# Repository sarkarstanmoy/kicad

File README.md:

# kicad
KiCad for electornics project

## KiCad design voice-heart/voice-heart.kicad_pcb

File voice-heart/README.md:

# Voice-Message Heart

A heart-shaped gift: press the big button in the middle and it plays a recorded voice
message while 10 red LEDs light up around the edge, stay on for about the length of the
message, then slowly fade out. Hold the small **REC** button to record a new message
(up to 10 s). The message stays even with the batteries removed.

| File | What it is |
|---|---|
| `voice-heart.kicad_pro` | KiCad 10 project (open this) |
| `voice-heart.kicad_sch` | Schematic, with supplier and price fields on every part |
| `voice-heart.kicad_pcb` | Heart-shaped 2-layer PCB, 96 x 86 mm, all through-hole |
| `voice-heart.kicad_sym` / `voice-heart.pretty/` | ISD1820 module symbol and footprint (blue 2x6-header board) |
| `voice-heart.kicad_dru` | Lion Circuits manufacturing limits as KiCad DRC rules |
| `docs/voice-heart-schematic.pdf` | Printable schematic |
| `docs/voice-heart-bom.csv` | Parts list |
| `docs/pcb-front.png`, `docs/pcb-back.png` | 3D renders |
| `fab/voice-heart-gerbers.zip` | Upload this to the PCB maker |

## How it works

| Block | Parts | What it does |
|---|---|---|
| Power | 3x AAA box with switch and screw lid (4.5 V) | No coin cells, so nothing small and dangerous to swallow |
| Voice | ISD1820 module (blue board) with its 8 Ω speaker plugged into the module | Records from its onboard mic while REC is held, plays the whole message on a PLAY press |
| Buttons | SW1 12 mm PLAY (front centre), SW2 6 mm REC (left lobe) | Both pull the module's REC/PLAYE pins up to the battery (active HIGH) |
| Glow timer | D11, D12, C1 22 µF, R11 470k, Q1 BC517 | A press charges C1; C1 drains slowly into Q1's base, so Q1 keeps the LEDs on about 10 s, then they fade over about 15 s |
| Heart LEDs | D1–D10 red 5 mm, R1–R10 330 Ω | About 6 mA each, about 60 mA total while glowing |

Want a longer glow? Swap C1 for 47 µF (about twice as long). Shorter? Use 10 µF.

Battery life: about 0 mA when idle (and the box has its own switch), about 80 mA while
playing. Hundreds of plays per set of AAAs.

## Ordering the board (Lion Circuits, cheapest settings)

Upload `fab/voice-heart-gerbers.zip` at [lioncircuits.com/quote](https://www.lioncircuits.com/quote)
and **keep every default**:

| Setting | Value |
|---|---|
| Quantity | 5 (minimum) |
| Board size | 96 x 86 mm (read from the Gerbers) |
| Layers | 2, single PCB, 1 design |
| Material / thickness | FR4-TG135, 1.6 mm |
| Copper / finish | 1 oz, HASL |
| Mask colour | **Green** (any other colour adds ₹500) |
| Service | Standard (5–6 days), DTDC Standard shipping (free) |

Quoted 13 Nov 2026: **₹1,652 + 18% GST = ₹1,949** for 5 boards, delivered.

The design is checked against Lion Circuits' standard limits (`voice-heart.kicad_dru`):
6 mil tracks/spacing, 12 mil via-to-track, 0.35 mm minimum drill, 6 mil annular ring,
6 mil silkscreen. The board uses 0.5 mm tracks, 0.3 mm spacing and 0.45 mm via drills, so
it passes with margin.

## Parts (about ₹250–350 plus the PCB)

See `docs/voice-heart-bom.csv`. Ask for the **blue ISD1820 module with speaker**
(Robu.in: "ISD1820 Recording Module Voice Board With On Board Mic and Loud Speaker"),
a **3x AAA box with switch and screw cover**, a BC517 Darlington transistor, and red
5 mm LEDs. No separate speaker is needed.

## Soldering order

Lowest parts first, so the board sits flat on the bench:

1. R1–R11 (resistors, standing upright). R11 is the 470k; the other ten are 330.
2. D11, D12 (1N4148): the black band goes on the side marked **K**.
3. Q1 (BC517): its flat face matches the silkscreen.
4. C1 (22 µF): the long leg (+) goes in the hole marked **+**.
5. D1–D10 (LEDs): the **long leg goes in the round pad**, the short leg in the square pad.
6. SW2 (REC) and SW1 (PLAY, big button).
7. Back side: solder a **2x6 female header** (or two 1x6 strips cut from a 1x40 strip)
   onto U1's 12 holes. The blue ISD1820 plugs in **component side down**, its header pins
   into this socket, so the module covers the back of the PLAY button. The socket
   height keeps the trimmed legs underneath clear of the module.
8. Speaker: plug its white connector into the module's speaker socket and glue the
   speaker to the back.
9. Battery box: red wire to **+**, black to **−** on the BATTERY pads. Glue the box to
   the back; it also works as a stand. A dab of hot glue over each wire joint stops the
   wires breaking.
10. Trim every leg flush on the back, then cover the back with felt or a 3D-printed
    plate so there are no sharp points.

> **Check before plugging in:** the back of the heart labels the module column
> **VCC, GND, FT, P-L, P-E, REC**, matching the blue ISD1820's own silkscreen. The other
> column ("JUMPERS") is the module's RPL/FT jumper pins and is not connected. **Remove
> any jumper caps** on the module, or it will loop or pass the mic through.

## Recording a message

1. Switch the battery box ON.
2. Hold **REC**, wait half a second, speak clearly about 10–20 cm from the module's mic,
   and let go within 10 seconds. The heart glows while you record.
3. Press the big heart button to hear it back.

Record again any time; the new message replaces the old one.

## Safety (for an 8-year-old)

- AAA box with a **screw-shut lid**: batteries can't fall out.
- No coin cells, no LiPo, nothing gets hot (about 80 mA from 4.5 V).
- Trim the legs and cover the back so there are no sharp points.
- Speaker volume is modest, comfortable at arm's length.

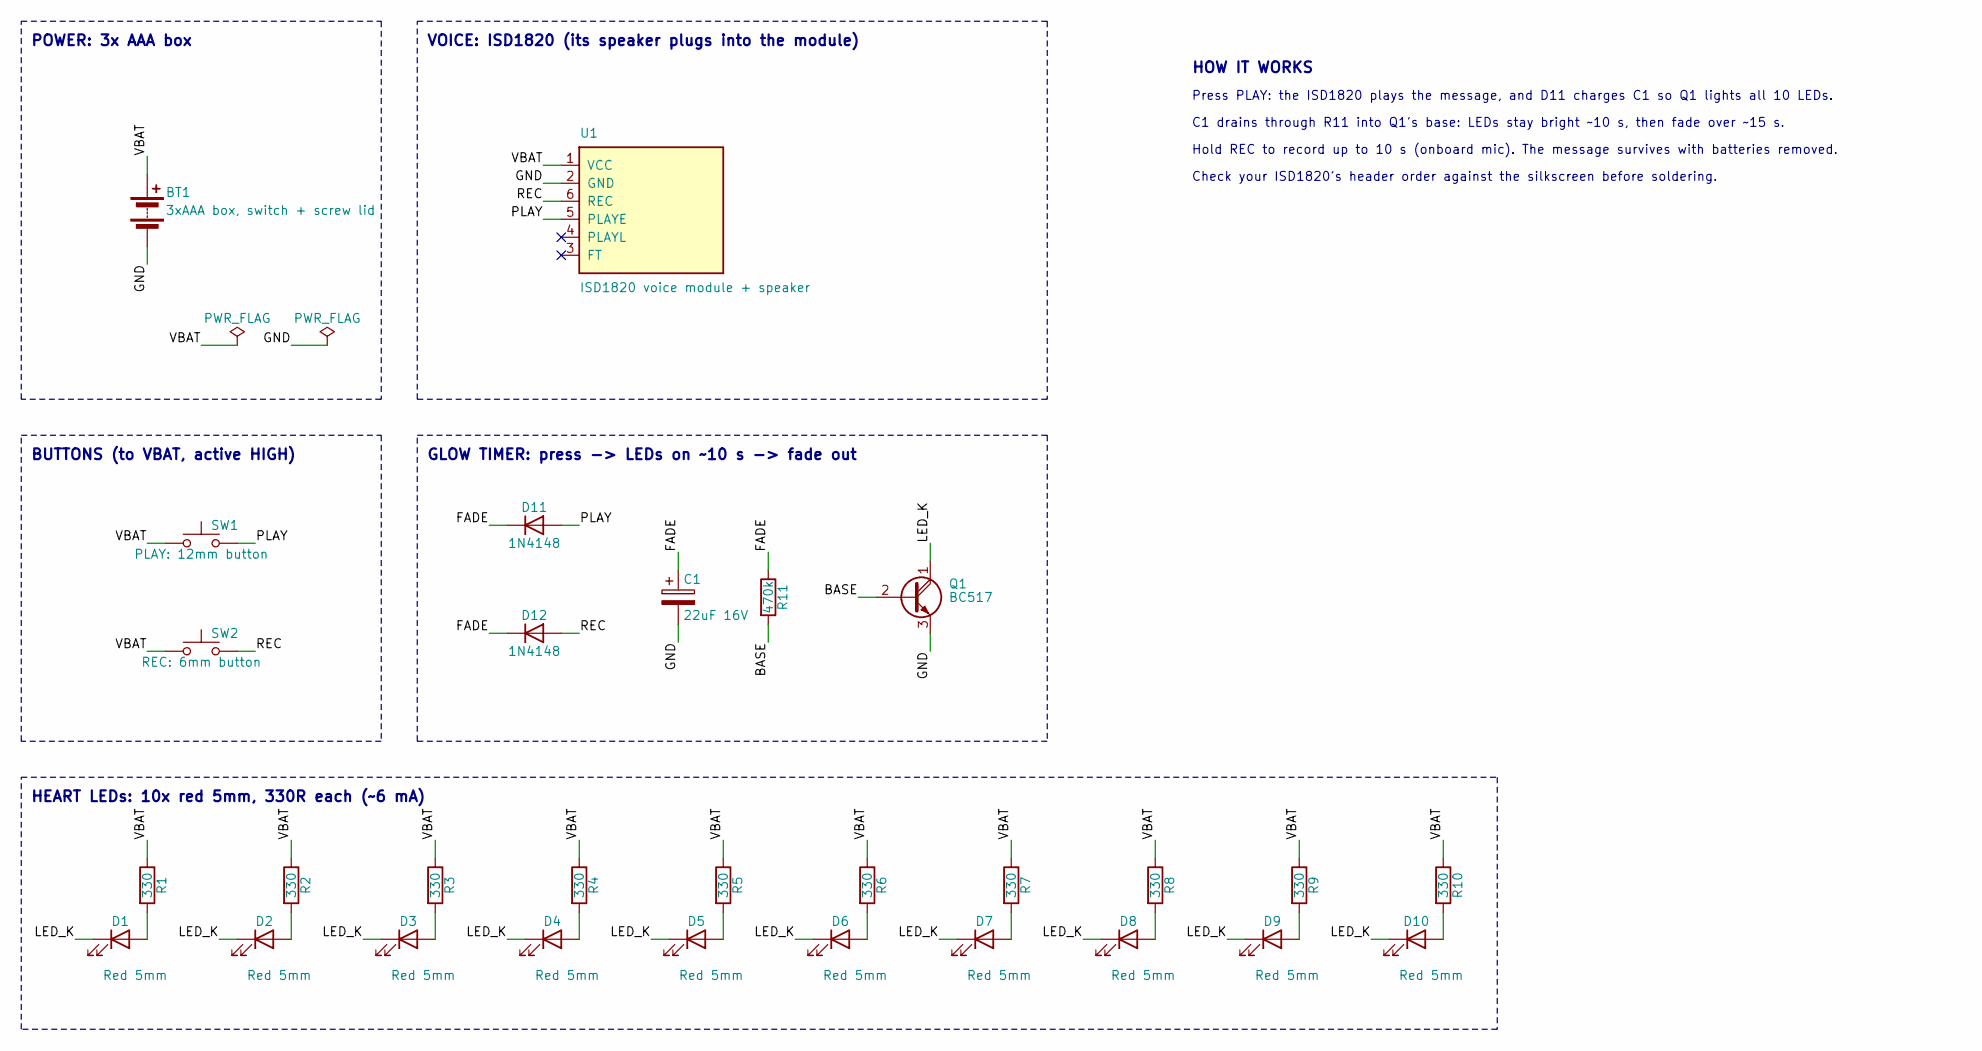
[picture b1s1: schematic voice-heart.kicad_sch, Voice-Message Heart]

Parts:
BT1: 3xAAA box, switch + screw lid; SolderWire-0.25sqmm_1x02_P4.2mm_D0.65mm_OD1.7mm
C1: 22uF 16V; CP_Radial_D5.0mm_P2.00mm
D1, D2, D3, D4, D5, D6, D7, D8, D9, D10: Red 5mm; LED_D5.0mm
D11, D12: 1N4148; D_DO-35_SOD27_P7.62mm_Horizontal
Q1: BC517; TO-92_Inline_Wide
R1, R2, R3, R4, R5, R6, R7, R8, R9, R10: 330; R_Axial_DIN0204_L3.6mm_D1.6mm_P2.54mm_Vertical
R11: 470k; R_Axial_DIN0204_L3.6mm_D1.6mm_P2.54mm_Vertical
SW1: PLAY: 12mm button; SW_PUSH-12mm
SW2: REC: 6mm button; SW_PUSH_6mm
U1: ISD1820 voice module + speaker; ISD1820_Module

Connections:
/BASE: Q1.2 (B), R11.2
/FADE: C1.1, D11.1 (K), D12.1 (K), R11.1
/GND: BT1.2 (-), C1.2, Q1.3 (E), U1.2 (GND)
/LED_K: D1.1 (K), D2.1 (K), D3.1 (K), D4.1 (K), D5.1 (K), D6.1 (K), D7.1 (K), D8.1 (K), D9.1 (K), D10.1 (K), Q1.1 (C)
/PLAY: D11.2 (A), SW1.2, U1.5 (PLAYE)
/REC: D12.2 (A), SW2.2, U1.6 (REC)
/VBAT: BT1.1 (+), R1.1, R2.1, R3.1, R4.1, R5.1, R6.1, R7.1, R8.1, R9.1, R10.1, SW1.1, SW2.1, U1.1 (VCC)
unnamed: D1.2 (A), R1.2
unnamed: D2.2 (A), R2.2
unnamed: D3.2 (A), R3.2
unnamed: D4.2 (A), R4.2
unnamed: D5.2 (A), R5.2
unnamed: D6.2 (A), R6.2
unnamed: D7.2 (A), R7.2
unnamed: D8.2 (A), R8.2
unnamed: D9.2 (A), R9.2
unnamed: D10.2 (A), R10.2

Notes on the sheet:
POWER: 3x AAA box
VOICE: ISD1820 (its speaker plugs into the module)
BUTTONS (to VBAT, active HIGH)
GLOW TIMER: press -> LEDs on ~10 s -> fade out
HEART LEDs: 10x red 5mm, 330R each (~6 mA)
HOW IT WORKS
Press PLAY: the ISD1820 plays the message, and D11 charges C1 so Q1 lights all 10 LEDs.
C1 drains through R11 into Q1's base: LEDs stay bright ~10 s, then fade over ~15 s.
Hold REC to record up to 10 s (onboard mic). The message survives with batteries removed.
Check your ISD1820's header order against the silkscreen before soldering.

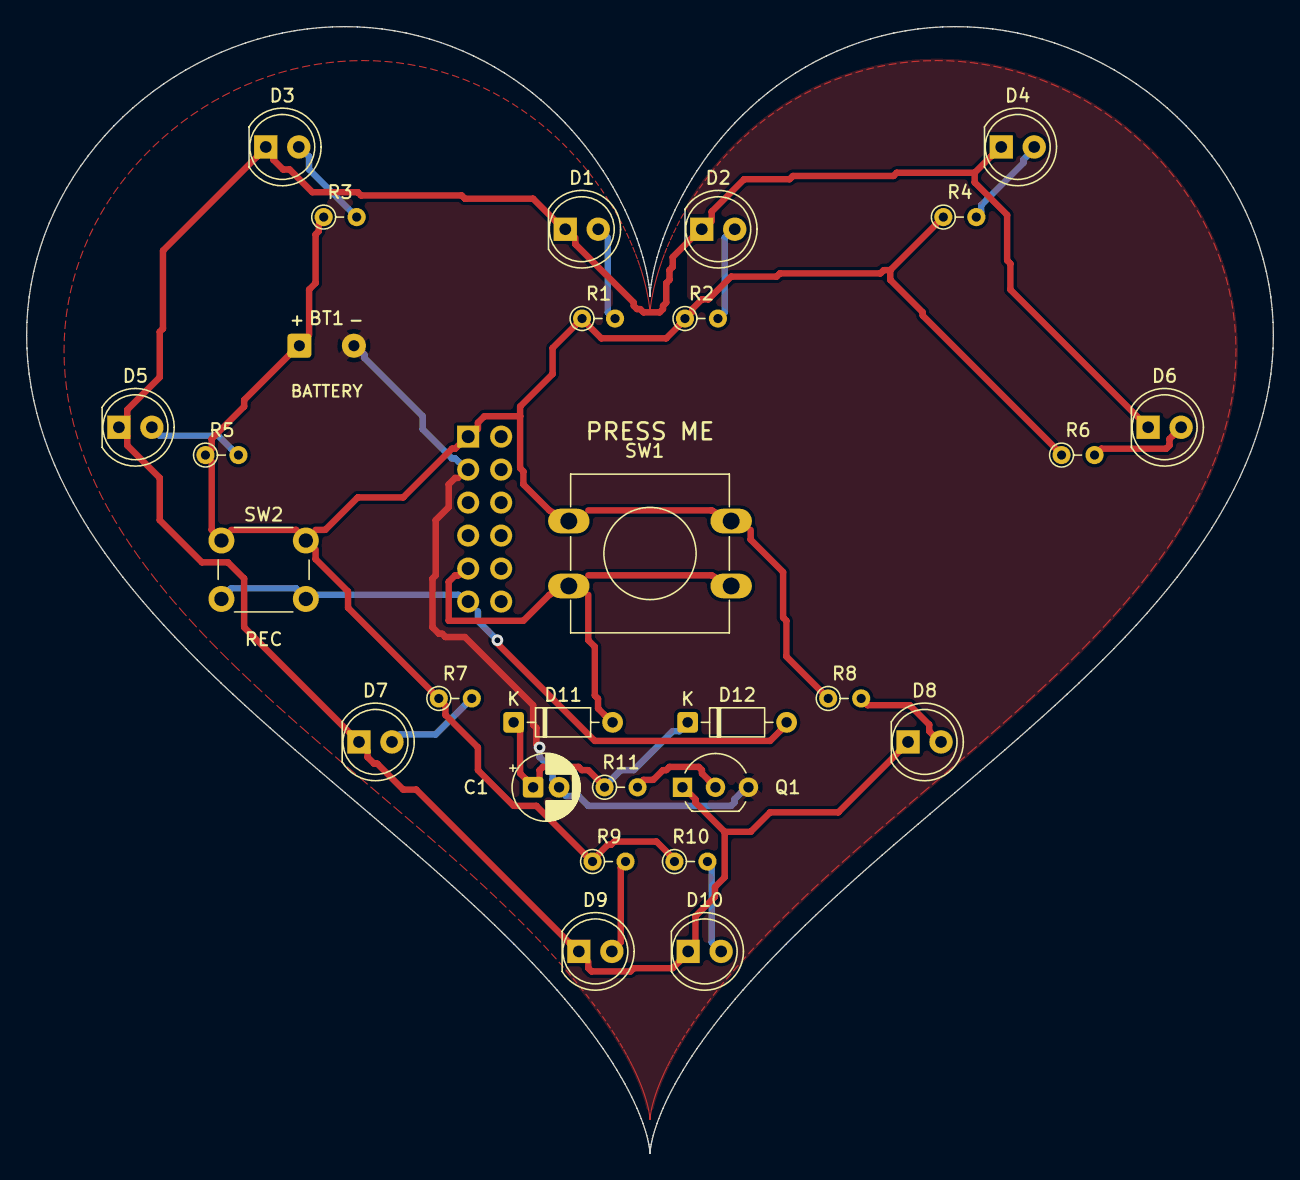
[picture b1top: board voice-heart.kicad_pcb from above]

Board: 2 copper layers, 96.0 x 86.8 mm, 29 parts (1 on the bottom side), 17 nets.

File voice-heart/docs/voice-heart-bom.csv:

"Refs","Part","Qty","Price (INR) each","Supplier","Footprint","Notes"
"BT1","3xAAA box, switch + screw lid","1","40-70","Robu.in / CTC Secunderabad","Connector_Wire:SolderWire-0.25sqmm_1x02_P4.2mm_D0.65mm_OD1.7mm","4.5V. Buy the box with a built-in ON/OFF switch and screw-on cover"
"C1","22uF 16V","1","2","Robu.in / CTC Secunderabad","Capacitor_THT:CP_Radial_D5.0mm_P2.00mm","Electrolytic. Bigger = longer glow (47uF is about twice as long)"
"D1-D10","Red 5mm","10","2","Robu.in / CTC Secunderabad","LED_THT:LED_D5.0mm","Diffused red; long leg = A (+)"
"D11,D12","1N4148","2","1","Robu.in / CTC Secunderabad","Diode_THT:D_DO-35_SOD27_P7.62mm_Horizontal","PLAY charges the timer,REC also lights the heart"
"Q1","BC517","1","5","Robu.in / CTC Secunderabad","Package_TO_SOT_THT:TO-92_Inline_Wide","NPN Darlington (gain > 30000) so a tiny current lights 10 LEDs"
"R1-R10","330","10","1","Robu.in / CTC Secunderabad","Resistor_THT:R_Axial_DIN0204_L3.6mm_D1.6mm_P2.54mm_Vertical","1/4W"
"R11","470k","1","1","Robu.in / CTC Secunderabad","Resistor_THT:R_Axial_DIN0204_L3.6mm_D1.6mm_P2.54mm_Vertical","Sets how fast the glow fades"
"SW1","PLAY: 12mm button","1","10-20","Robu.in / CTC Secunderabad","Button_Switch_THT:SW_PUSH-12mm","12x12mm tactile with a coloured cap"
"SW2","REC: 6mm button","1","5","Robu.in / CTC Secunderabad","Button_Switch_THT:SW_PUSH_6mm","Hold to record (up to 10 s)"
"U1","ISD1820 voice module + speaker","1","159","Robu.in","voice-heart:ISD1820_Module","Blue 2x6-header board with 8ohm speaker; leave RPL/FT jumpers off"

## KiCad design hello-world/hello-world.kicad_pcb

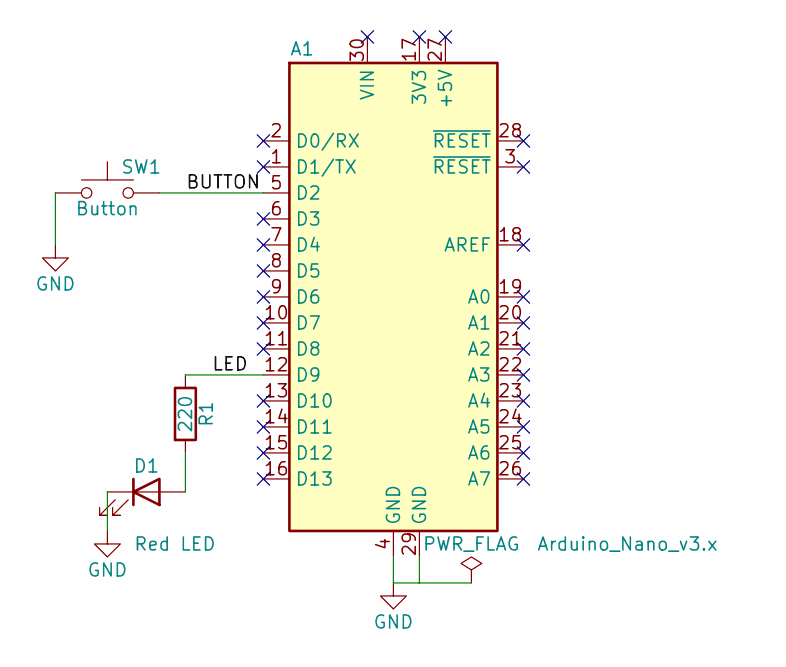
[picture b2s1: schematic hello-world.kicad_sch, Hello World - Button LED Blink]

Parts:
A1: Arduino_Nano_v3.x; Arduino_Nano
D1: Red LED; LED_D5.0mm
R1: 220; R_Axial_DIN0207_L6.3mm_D2.5mm_P10.16mm_Horizontal
SW1: Button; SW_PUSH_6mm

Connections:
/BUTTON: A1.5 (D2), SW1.2
/LED: A1.12 (D9), R1.1
GND: A1.4 (GND), A1.29 (GND), D1.1 (K), SW1.1
unnamed: D1.2 (A), R1.2

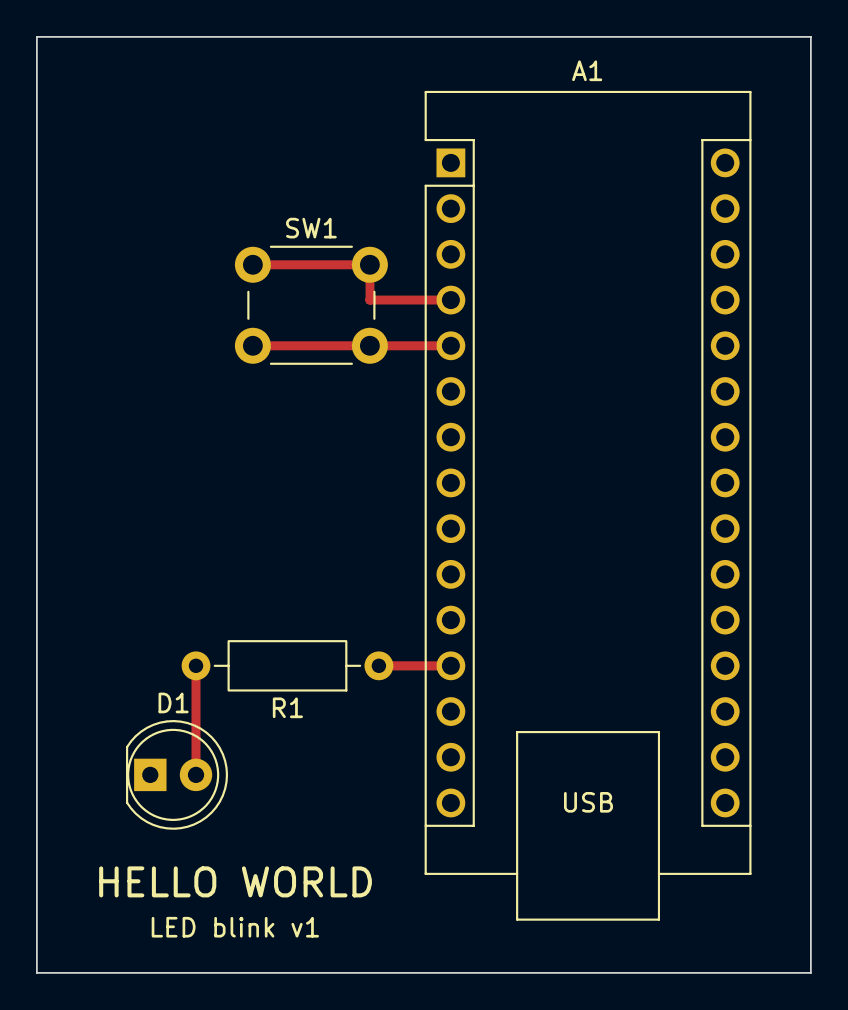
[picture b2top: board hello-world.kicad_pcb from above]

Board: 2 copper layers, 43.0 x 52.0 mm, 4 parts (0 on the bottom side), 4 nets.

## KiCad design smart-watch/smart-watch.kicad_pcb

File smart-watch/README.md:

# Smart Watch v0.1 (module build)

A beginner-friendly smartwatch built from ready-made modules, hand-wired on perfboard
with 30 AWG silicone wire. No SMD soldering needed.

| File | What it is |
|---|---|
| `smart-watch.kicad_pro` | KiCad 10 project (open this) |
| `smart-watch.kicad_sch` | Schematic: every connection, part values, supplier and price fields |
| `smart-watch.kicad_sym` / `smart-watch.pretty/` | Project library: module symbols and footprints |
| `docs/smart-watch-schematic.pdf` | Printable schematic for the workbench |
| `docs/smart-watch-bom.csv` | Bill of materials exported from the schematic |
| `smart-watch.kicad_pcb` | 2-layer carrier PCB, 62 x 46 mm, all through-hole |
| `fab/smart-watch-gerbers.zip` | Gerbers + drill file, ready to upload to JLCPCB / PCBWay |
| `docs/pcb-top.png`, `docs/pcb-bottom.png` | 3D renders of the board |

## Specifications

| | |
|---|---|
| MCU | ESP32-C3 (RISC-V 160 MHz, Wi-Fi 2.4 GHz + BLE 5) on a SuperMini board |
| Display | 0.96" SSD1306 OLED, 128x64, I2C address `0x3C` |
| Timekeeping | DS3231 RTC (±2 ppm, about ±1 min/year), I2C `0x68`, own CR1220 backup cell |
| Time sync | NTP over Wi-Fi (optional) |
| Inputs | 3 tactile buttons: Up, Select, Down. Each one wakes the watch from deep sleep |
| Battery | 3.7 V LiPo, 300–500 mAh, JST-PH 2.0 lead |
| Charging | TP4056 module, USB-C, 1 A max (DW01 over-charge, over-discharge and short protection) |
| Power switch | Slide switch between the charger output and the ESP32 |
| Battery monitor | 1:2 divider on GPIO0 (ADC1) |
| Approx. size | Stack of ~35 x 30 x 15 mm before the case |

## Pin assignments (ESP32-C3 SuperMini)

| Pin | Net | Connected to | Why this pin |
|---|---|---|---|
| 5V | VSYS | D1 cathode | Battery feeds the board's onboard 3.3 V regulator |
| 3V3 | +3V3 | OLED VCC, RTC + | Regulated 3.3 V for both I2C modules |
| GND | GND | Everything's ground, TP4056 OUT- | |
| GPIO0 | BAT_ADC | R1/R2 midpoint, C1 | ADC1 channel, still works while Wi-Fi is on |
| GPIO3 | BTN_UP | SW1 to GND | Can wake from deep sleep (GPIO0–5 only) |
| GPIO4 | BTN_SELECT | SW2 to GND | Can wake from deep sleep |
| GPIO5 | BTN_DOWN | SW3 to GND | Can wake from deep sleep |
| GPIO6 | I2C_SDA | OLED SDA, RTC D | Not a strapping pin |
| GPIO7 | I2C_SCL | OLED SCL, RTC C | Not a strapping pin |
| GPIO1, GPIO10 | (spare) | | Free for a buzzer or vibration motor later |
| GPIO2, 8, 9 | (unused) | | Strapping pins; GPIO8 drives the onboard LED, GPIO9 is BOOT |
| GPIO20, 21 | (unused) | | UART RX/TX |

> Clone boards differ. Wire by the labels printed on your modules, not by pin position.
> The OLED in particular may be `VCC GND SCL SDA` instead of `GND VCC SCL SDA`.

Firmware pin map for the Arduino IDE (board: **ESP32C3 Dev Module**, USB CDC On Boot: Enabled):

```cpp
#define PIN_BAT_ADC   0
#define PIN_BTN_UP    3
#define PIN_BTN_SEL   4
#define PIN_BTN_DOWN  5
#define PIN_SDA       6
#define PIN_SCL       7
// Wire.begin(PIN_SDA, PIN_SCL);
// Buttons: pinMode(pin, INPUT_PULLUP); pressed = LOW
// Deep sleep: esp_deep_sleep_enable_gpio_wakeup((1<<3)|(1<<4)|(1<<5), ESP_GPIO_WAKEUP_GPIO_LOW);
// Battery volts = analogReadMilliVolts(PIN_BAT_ADC) * 2 / 1000.0
```

## Wiring list

| # | From | To | Net |
|---|---|---|---|
| 1 | LiPo red (+) | TP4056 B+ | BAT+ |
| 2 | LiPo black (-) | TP4056 B- | BAT- |
| 3 | TP4056 OUT+ | Slide switch middle pin | BAT_OUT |
| 4 | Slide switch outer pin | D1 anode | VSW |
| 5 | D1 cathode (band) | ESP32 5V | VSYS |
| 6 | TP4056 OUT- | ESP32 GND | GND |
| 7 | ESP32 3V3 | OLED VCC and RTC + | +3V3 |
| 8 | ESP32 GND | OLED GND and RTC - | GND |
| 9 | ESP32 GPIO6 | OLED SDA and RTC D | I2C_SDA |
| 10 | ESP32 GPIO7 | OLED SCL and RTC C | I2C_SCL |
| 11 | ESP32 GPIO3 / 4 / 5 | One leg of SW1 / SW2 / SW3 | BTN_* |
| 12 | Other leg of each button | GND | GND |
| 13 | VSW (switch outer pin) | R1 (100k) to R2 (100k) to GND | BAT_ADC at the middle |
| 14 | R1/R2 midpoint | ESP32 GPIO0, plus C1 (100nF) to GND | BAT_ADC |

Never connect B- to OUT-: the protection chip sits between them.

## PCB (optional instead of perfboard)

| | |
|---|---|
| Size | 62 x 46 mm, 2 layers, 1.6 mm FR-4 |
| Tracks | 0.4 mm wide, 0.2 mm clearance, 6 vias (0.8 mm pad / 0.4 mm drill) |
| GND | Copper pour on both layers |
| Checks | ERC 0 violations; DRC 0 violations, 0 unconnected, matches the schematic |

Layout: TP4056 top-left (USB-C on the left edge for charging), ESP32-C3 top-right (USB-C
on the top edge for programming), battery JST, power switch and D1 in between, buttons
along the bottom. The OLED's 4-pin header sits below the ESP32. Use long pins (11 mm) so
the 27 x 27 mm OLED module stacks **over** the ESP32, header at the bottom. The display is
then upside down, so call `display.setRotation(2)`. The outline is on the `Dwgs.User` layer.

To order: upload `fab/smart-watch-gerbers.zip` to JLCPCB/PCBWay with the default settings
(2 layers, 1.6 mm, HASL). This is a module carrier, bigger than a final watch: it's for
proving the circuit before squeezing it into a case.

> Before ordering, hold your modules against a 1:1 printout of the board (KiCad: File →
> Print, scale 1:1). The ESP32-C3 SuperMini row spacing (15.24 mm) and the TP4056 pad
> positions are from typical clones and may differ on yours.

## Power budget (estimate)

| State | Current | Notes |
|---|---|---|
| Deep sleep | ~0.2 mA | ESP32 ~5 µA, regulator ~40 µA, DS3231 ~110 µA, divider ~19 µA, OLED off ~10 µA |
| Screen on, Wi-Fi off | ~30–40 mA | Short glance when a button is pressed |
| Wi-Fi time sync | ~100 mA avg, 350 mA peaks | Once a day for ~10 s |
| SuperMini red power LED | +1–2 mA always | Remove it (desolder or scrape) for real battery life |

Example day with a 400 mAh cell: deep sleep 24 h (~4.8 mAh), 30 glances of 5 s (~1.5 mAh)
and one Wi-Fi sync (~0.3 mAh) comes to about 6.6 mAh/day, so **roughly 6–8 weeks per charge**
once the power LED is removed. With the LED left on, expect about 1–2 weeks.

Low-battery limit: D1 drops ~0.2–0.3 V and the board's regulator needs ~3.4 V, so the watch
can reset during Wi-Fi bursts once the cell falls below ~3.6–3.7 V. Show a "charge me"
warning at 3.7 V. A later revision could swap D1 for a P-MOSFET "ideal diode" to recover
that headroom.

## Shopping list

The electronic parts are in `docs/smart-watch-bom.csv`. You'll also need:

| Item | Approx. price (INR) |
|---|---|
| 30 AWG silicone wire, small perfboard | 50–100 |
| 20/22 mm watch strap | 150–300 |
| 3D-printed case (Thingiverse/Printables STL, printed by Robu.in or a local service) | 200–500 |
| CR1220 cell for the DS3231 mini (if not included) | 20–40 |

Total with the modules: roughly ₹1,500–2,500. Tools (if needed): soldering iron kit,
multimeter, hot glue gun, wire stripper.

Where to buy: Robu.in, Robocraze, ElectronicsComp, Probots, Evelta, Amazon.in (check reviews),
or Chenoy Trade Centre (CTC) in Secunderabad.

## Build order

1. **Breadboard:** ESP32-C3 + OLED + RTC on I2C (GPIO6/7). Show the time using the
   `Adafruit_SSD1306` and `RTClib` libraries. Power from the ESP32's USB.
2. **Buttons and sleep:** add SW1–SW3 and deep sleep, and wake on any button.
3. **Battery:** add LiPo, TP4056, slide switch, D1 and the battery divider. Check with a
   multimeter that VSYS reads about 3.5–4.0 V **before** connecting the ESP32.
4. **Final assembly:** solder everything with thin wire, insulate with Kapton tape or heat
   shrink, fit it into the case and attach the strap.

## Safety

- Never puncture, bend, crush or short-circuit the LiPo. Keep it away from the soldering iron.
- Only use a TP4056 module **with** protection (DW01 + 8205A chips next to the B+/B- pads).
- Check battery polarity with a multimeter: some JST leads are wired backwards.
- Don't charge the watch unattended or while wearing it during the first tests.

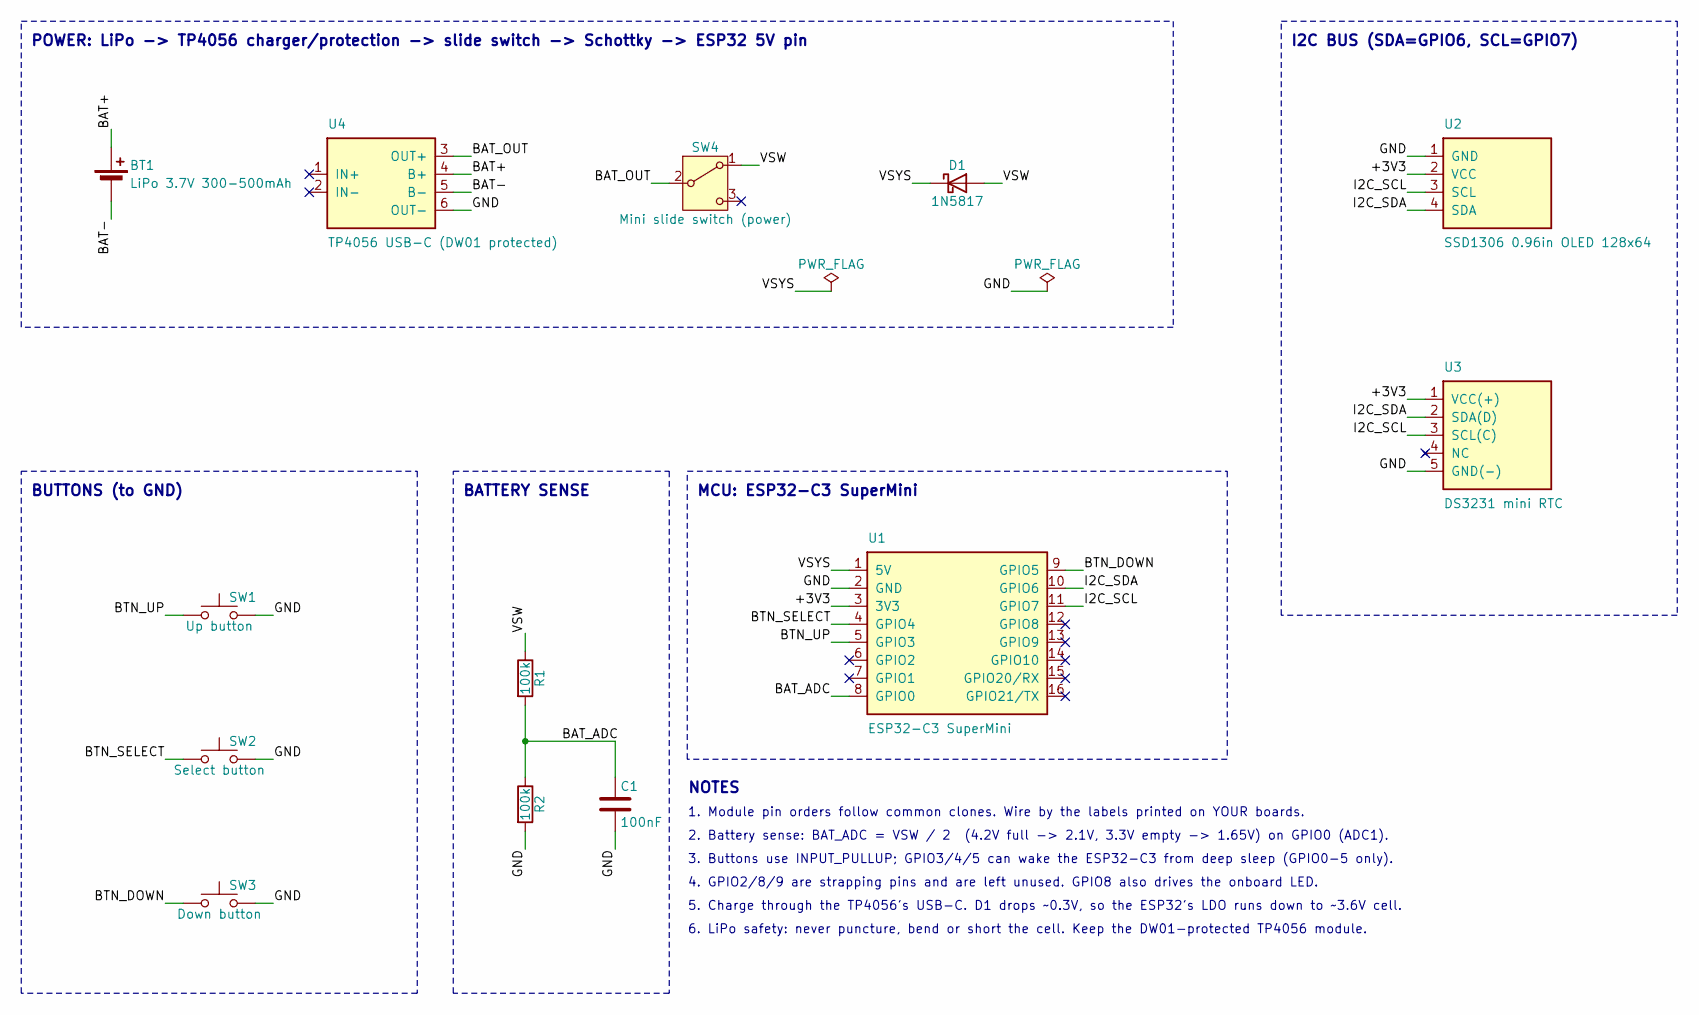
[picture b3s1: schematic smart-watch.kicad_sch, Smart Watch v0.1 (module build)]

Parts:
BT1: LiPo 3.7V 300-500mAh; JST_PH_B2B-PH-K_1x02_P2.00mm_Vertical
C1: 100nF; C_Disc_D3.0mm_W1.6mm_P2.50mm
D1: 1N5817; D_DO-41_SOD81_P10.16mm_Horizontal
R1, R2: 100k; R_Axial_DIN0207_L6.3mm_D2.5mm_P7.62mm_Horizontal
SW1: Up button; SW_PUSH_6mm
SW2: Select button; SW_PUSH_6mm
SW3: Down button; SW_PUSH_6mm
SW4: Mini slide switch (power); SW_Slide_SPDT_Straight_CK_OS102011MS2Q
U1: ESP32-C3 SuperMini; ESP32-C3_SuperMini
U2: SSD1306 0.96in OLED 128x64; PinHeader_1x04_P2.54mm_Vertical
U3: DS3231 mini RTC; PinHeader_1x05_P2.54mm_Vertical
U4: TP4056 USB-C (DW01 protected); TP4056_TypeC_Module

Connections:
/+3V3: U1.3 (3V3), U2.2 (VCC), U3.1 (VCC(+))
/BAT+: BT1.1 (+), U4.4 (B+)
/BAT-: BT1.2 (-), U4.5 (B-)
/BAT_ADC: C1.1, R1.2, R2.1, U1.8 (GPIO0)
/BAT_OUT: SW4.2 (B), U4.3 (OUT+)
/BTN_DOWN: SW3.1, U1.9 (GPIO5)
/BTN_SELECT: SW2.1, U1.4 (GPIO4)
/BTN_UP: SW1.1, U1.5 (GPIO3)
/GND: C1.2, R2.2, SW1.2, SW2.2, SW3.2, U1.2 (GND), U2.1 (GND), U3.5 (GND(-)), U4.6 (OUT-)
/I2C_SCL: U1.11 (GPIO7), U2.3 (SCL), U3.3 (SCL(C))
/I2C_SDA: U1.10 (GPIO6), U2.4 (SDA), U3.2 (SDA(D))
/VSW: D1.2 (A), R1.1, SW4.1 (A)
/VSYS: D1.1 (K), U1.1 (5V)

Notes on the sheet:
POWER: LiPo -> TP4056 charger/protection -> slide switch -> Schottky -> ESP32 5V pin
MCU: ESP32-C3 SuperMini
I2C BUS (SDA=GPIO6, SCL=GPIO7)
BUTTONS (to GND)
BATTERY SENSE
NOTES
1. Module pin orders follow common clones. Wire by the labels printed on YOUR boards.
2. Battery sense: BAT_ADC = VSW / 2 (4.2V full -> 2.1V, 3.3V empty -> 1.65V) on GPIO0 (ADC1).
3. Buttons use INPUT_PULLUP; GPIO3/4/5 can wake the ESP32-C3 from deep sleep (GPIO0-5 only).
4. GPIO2/8/9 are strapping pins and are left unused. GPIO8 also drives the onboard LED.
5. Charge through the TP4056's USB-C. D1 drops ~0.3V, so the ESP32's LDO runs down to ~3.6V cell.
6. LiPo safety: never puncture, bend or short the cell. Keep the DW01-protected TP4056 module.

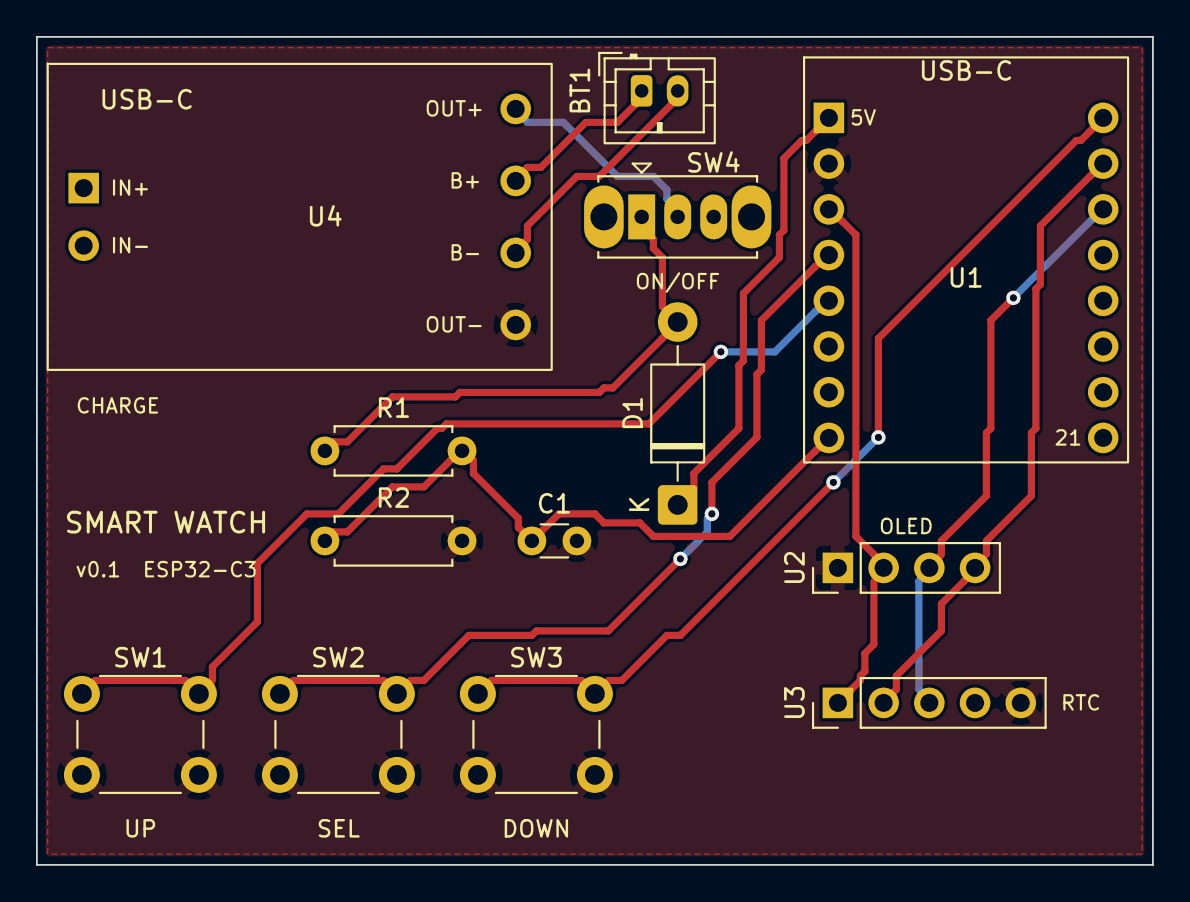
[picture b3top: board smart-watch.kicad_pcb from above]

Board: 2 copper layers, 62.0 x 46.0 mm, 13 parts (0 on the bottom side), 13 nets.
